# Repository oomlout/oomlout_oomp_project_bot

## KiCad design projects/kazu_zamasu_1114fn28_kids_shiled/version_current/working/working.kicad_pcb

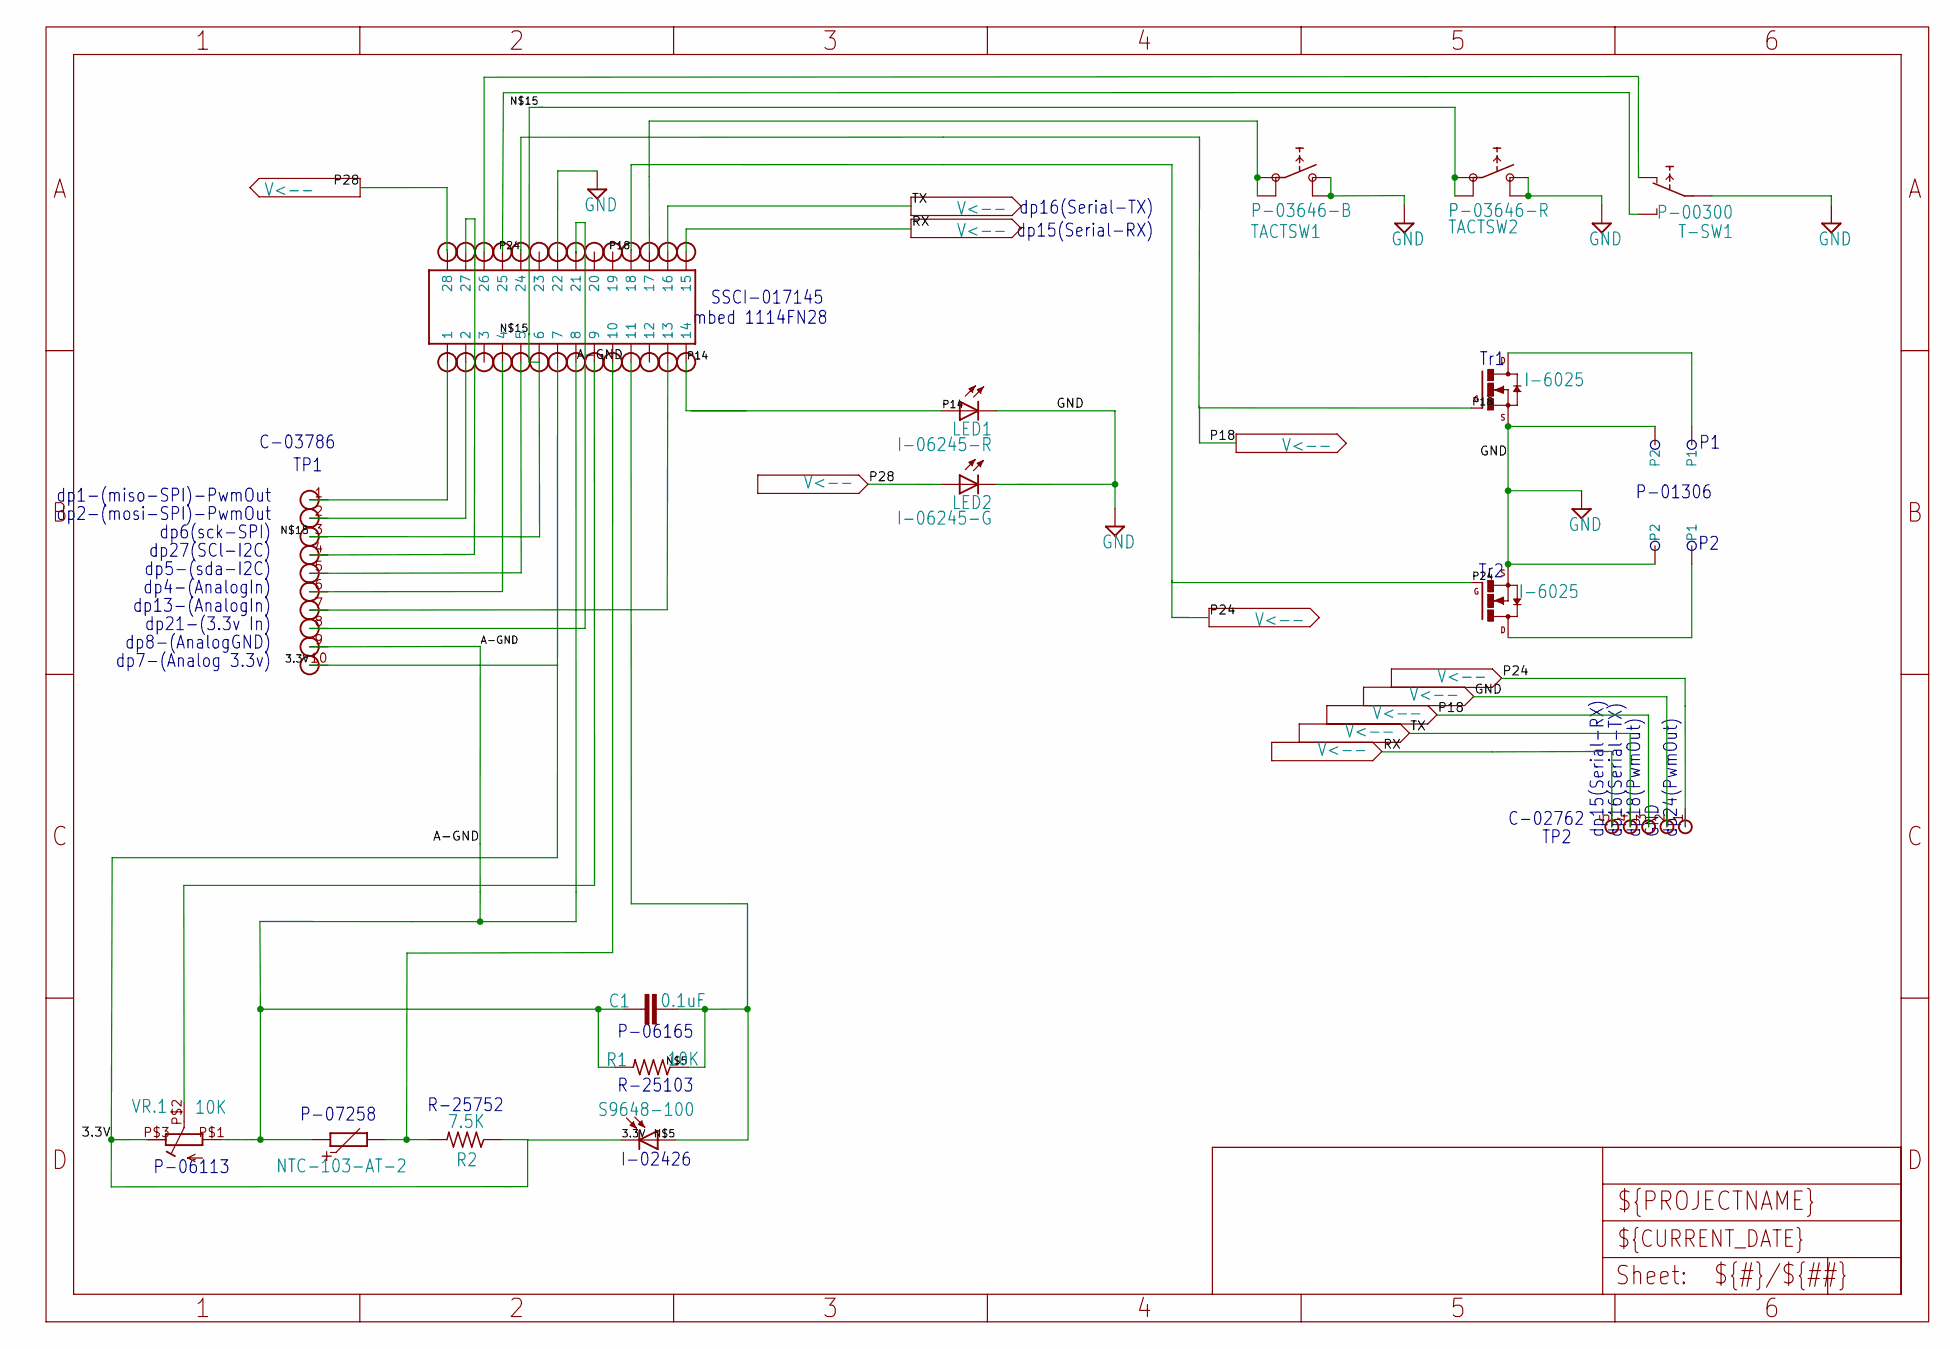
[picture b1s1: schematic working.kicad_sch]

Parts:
C1: 0.1uF; C
LED1: I-06245-R; LED5MM
LED2: I-06245-G; LED5MM
R1: 10K; R12MM
R2: 7.5K; R12MM
T-SW1: P-00300; TOGLE-SW
TACTSW1: P-03646-B; TACT-SW
TACTSW2: P-03646-R; TACT-SW
TB1, TB2: P-01306; TB
U$1: FH-1X14; DIP28-SOCKET
U$2: S9648-100; PHOTO-IC
U$3: SIPS-5
U$4, U$5: I-6025; TO251AA
U$8: SIPS-10
UNK0-50C0: NTC-103-AT-2; NTC
VR.1: 10K; VOL-TRIM

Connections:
3.3V: R2.1, U$1.P$7 (7), U$2.P$2 (C), U$8.10, VR.1.P$3 (E)
A-GND: C1.1, R1.2, U$1.P$8 (8), U$8.9, UNK0-50C0.1, VR.1.P$1 (A)
GND: LED1.K (C), LED2.K (C), T-SW1.P$2 (2COM), TACTSW1.1 (4), TACTSW1.2, TACTSW2.1 (4), TACTSW2.2, TB1.P$2 (P2), TB2.P$2 (P2), U$1.P$22 (22), U$3.2, U$4.3 (S), U$5.3 (S)
unnamed: C1.2, R1.1, U$1.P$11 (11), U$2.P$1 (A)
unnamed: U$1.P$9 (9), VR.1.P$2 (S)
unnamed: TACTSW1.3, TACTSW1.4 (1), U$1.P$17 (17)
unnamed: U$1.P$1 (1), U$8.1
unnamed: U$1.P$5 (5), U$8.5
unnamed: U$1.P$27 (27), U$8.4
unnamed: T-SW1.P$3 (3), U$1.P$25 (25)
unnamed: U$1.P$2 (2), U$8.2
unnamed: TACTSW2.3, TACTSW2.4 (1), U$1.P$6 (6), U$8.3
unnamed: U$1.P$4 (4), U$8.6
unnamed: T-SW1.P$1 (1), U$1.P$26 (26)
unnamed: TB2.P$1 (P1), U$5.2 (D), U$5.4 (D)
unnamed: TB1.P$1 (P1), U$4.2 (D), U$4.4 (D)
unnamed: U$1.P$13 (13), U$8.7
unnamed: R2.2, U$1.P$10 (10), UNK0-50C0.2
unnamed: U$1.P$21 (21), U$8.8
P14: LED1.A, U$1.P$14 (14)
P28: LED2.A, U$1.P$28 (28)
RX: U$1.P$15 (15), U$3.5
TX: U$1.P$16 (16), U$3.4

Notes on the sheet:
TP1
dp18(PwmOut)
P-06165
P-07258
R-25752
TP2
I-02426
SSCI-017145
dp21-(3.3v In)
R-25103
P-01306
dp4-(AnalogIn)
dp24(PwmOut)
GND
dp27(SCl-I2C)
Tr2
dp2-(mosi-SPI)-PwmOut
dp16(Serial-TX)
dp8-(AnalogGND)
P-06113
dp7-(Analog 3.3v)
dp13-(AnalogIn)
C-02762
dp15(Serial-RX)
mbed 1114FN28
C-03786
dp6(sck-SPI)
dp5-(sda-I2C)
dp1-(miso-SPI)-PwmOut
Tr1

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
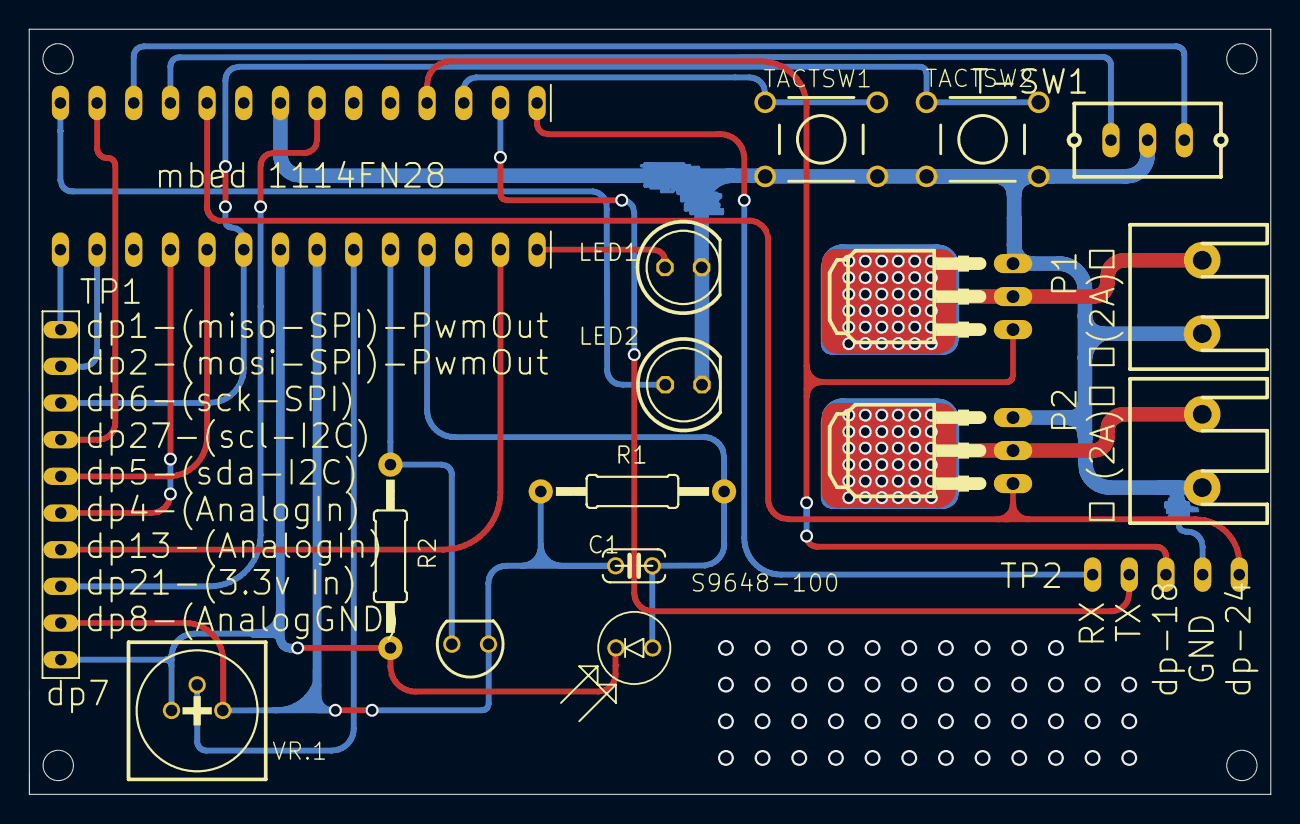
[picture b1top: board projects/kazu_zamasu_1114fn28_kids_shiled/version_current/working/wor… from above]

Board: 2 copper layers, 86.0 x 53.0 mm, 23 parts (1 on the bottom side), 25 nets.

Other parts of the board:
@HOLE0, @HOLE1, @HOLE2, @HOLE3: (no value)
U$7: A4L-LOC

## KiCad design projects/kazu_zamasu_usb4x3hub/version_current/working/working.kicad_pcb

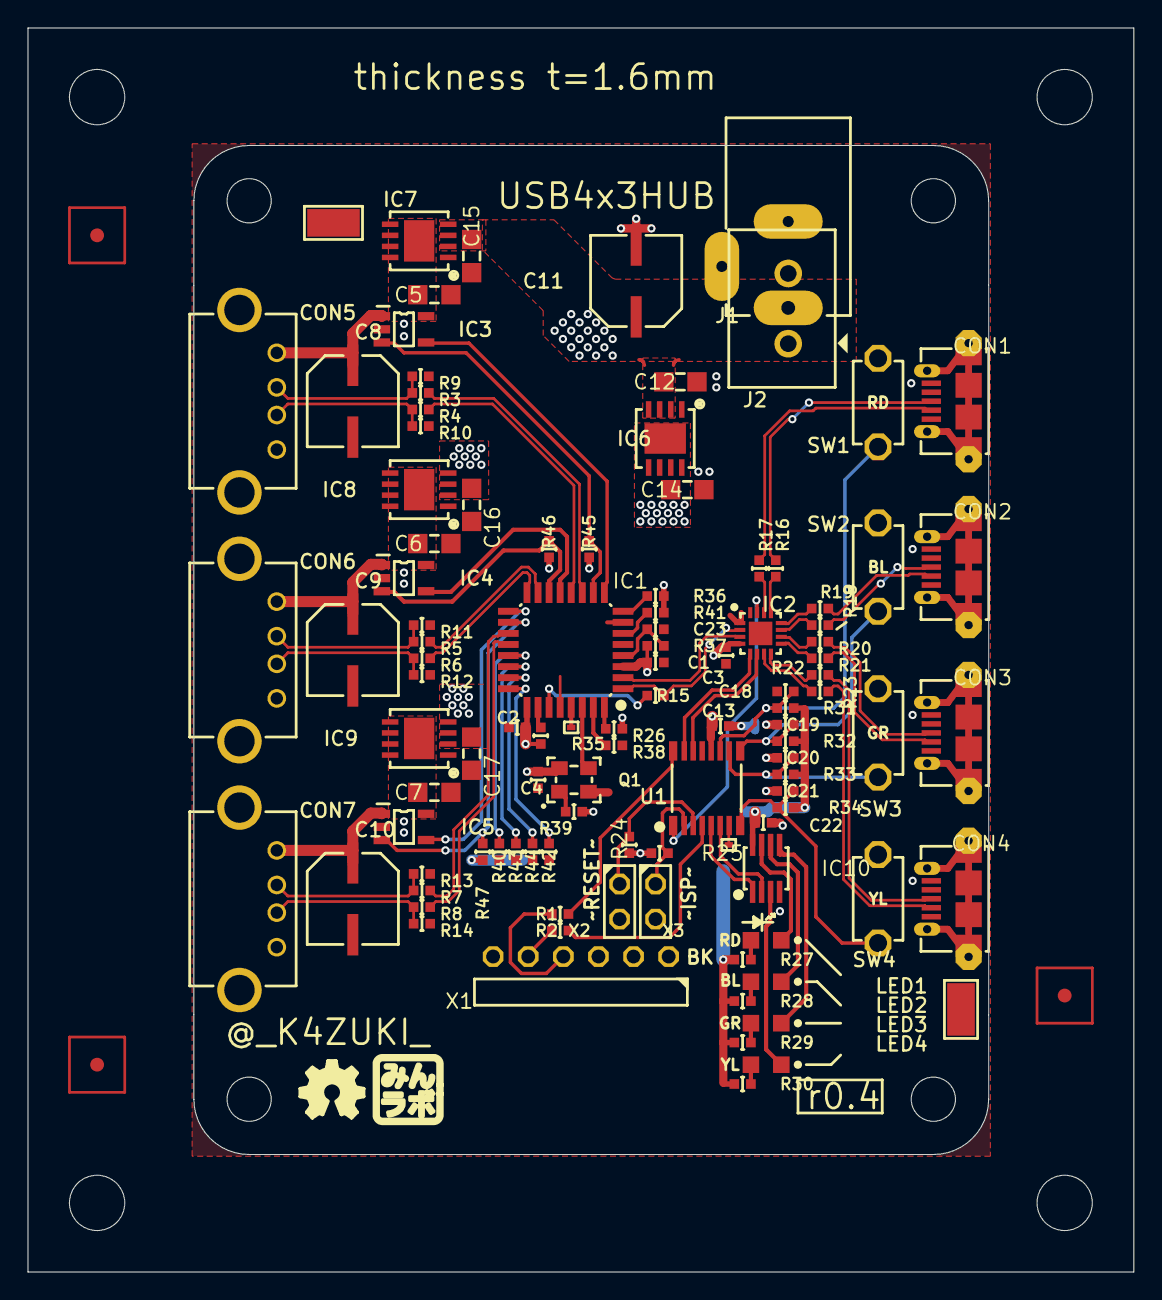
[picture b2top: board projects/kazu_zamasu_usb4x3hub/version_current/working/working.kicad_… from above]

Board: 2 copper layers, 80.0 x 90.0 mm, 121 parts (0 on the bottom side), 87 nets.

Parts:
@HOLE0, @HOLE1, @HOLE2, @HOLE3: (no value)
C1, C2, C3, C4, C13, C22: C0402
C5, C6, C7, C12, C14, C15, C16, C17: 4.7u/2012; CR_2125
C8, C9, C10, C11: 100u/OS-CON; C_2.5PHI6.3_C6
C18, C19, C20, C21: 0.1u/1005; C0402
C23: 1u/1005; C0402
CON1, CON2, CON3, CON4: CON_USB_47589-0001MOLEX
CON5, CON6, CON7: CON_USB_A_SHIELD
GIT1: 27149e3; GIT-REVISION
I1: ICON_MINLAB_5.2MM
IC1: TUSB2036; QFP32_0.8P7.2X7.2
IC2: FSUSB74MPX; QFN16_0.5P3.0X3.0
IC3, IC4, IC5: TPS2041C; IC_05_0.95_50MIL
IC6: 3.3V; DFN80P410X410_8N
IC7, IC8, IC9: 5V; DFN80P410X410_8N
IC10: SN74LVC1G139DCUR; SOT65P315X290-8N
ICON1: OSHW; ICON_OSHW
ICON2: r0.4; ICON_REVISION2.0
J1: CON_DCJACK_C-1604
J2: TB111-2-2-U-1-1
LED1: RD; CHIPLED_0805
LED2: BL; CHIPLED_0805
LED3: GR; CHIPLED_0805
LED4: YL; CHIPLED_0805
P1, P2, P3, P4: PCB_CORNER
Q1: OSC4_48M; CLOCK_2520
R1, R2, R9, R10, R11, R12, R13, R14, R24, R25, R26, R27, R28, R29, R30, R31, R32, R33, R34, R35, R36, R37, R38, R40, R41, R42, R43, R44, R45, R46, R47: C0402
R3, R4, R5, R6, R7, R8, R16, R17, R18, R19, R20, R21, R22, R23: 33/1005; C0402
R15: 1.5k/1005; C0402
R39: 10k/1005; C0402
SW1: RD; SW_TACTSW_P8073
SW2: BL; SW_TACTSW_P8073
SW3: GR; SW_TACTSW_P8073
SW4: YL; SW_TACTSW_P8073
TP1, TP2: TP_4020
TP3, TP4: TP06RECT
TP100, TP101, TP102: FIDUCIAL
U1: LPC812M101JDH16; SOT65P510X450X110-16N
X1: TSW-106-02-S-S-RA
X2, X3: TSW-102-02-S-S

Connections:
3.3V: C1.1, C2.1, C3.1, C4.1, C13.2, C14.1, C22.1, IC1.3, IC1.25, IC2.4, IC6.5, IC6.6, IC6.7, IC6.EP, IC10.8, Q1.4, R24.2, R25.2, R26.1, R27.2, R28.2, R29.2, R30.2, R31.2, R32.2, R33.2, R34.2, R35.1, R36.1, R37.1, R39.1, R41.2, R45.2, R46.2, R47.2, U1.12
5V1: C5.1, IC3.5, IC7.5, IC7.6, IC7.7, IC7.EP
5V2: C6.1, IC4.5, IC8.5, IC8.6, IC8.7, IC8.EP
5V3: C7.1, IC5.5, IC9.5, IC9.6, IC9.7, IC9.EP
->TX: R1.1, X1.4
<-RX: R2.1, X1.5
GND: C1.2, C2.2, C3.2, C4.2, C5.2, C6.2, C7.2, C8.-, C9.-, C10.-, C11.-, C12.2, C13.1, C14.2, C15.2, C16.2, C17.2, C18.2, C19.2, C20.2, C21.2, C22.2, C23.2, CON1.5, CON2.5, CON3.5, CON4.5, CON5.4, CON6.4, CON7.4, IC1.7, IC1.28, IC2.1, IC3.2, IC4.2, IC5.2, IC6.1, IC7.1, IC8.1, IC9.1, IC10.4, J1.1, J2.2, Q1.2, R9.1, R10.1, R11.1, R12.1, R13.1, R14.1, R38.1, R40.1, R42.1, R43.1, R44.1, SW1.A1, SW2.A1, SW3.A1, SW4.A1, TP1.TP, TP2.TP, U1.13, X1.1, X2.2, X3.2
ISP: R25.1, U1.2, X3.1
LSEL1: IC10.1, U1.5
LSEL2: IC10.2, U1.6
unnamed: IC1.1, IC2.2, R15.1
unnamed: IC1.2, IC2.3
unnamed: CON1.3, R16.1
unnamed: CON1.2, R17.1
unnamed: CON2.3, R18.1
unnamed: CON2.2, R19.1
unnamed: CON3.3, R20.1
unnamed: CON4.3, R22.1
unnamed: CON3.2, R21.1
unnamed: CON4.2, R23.1
unnamed: C8.+, CON5.1, IC3.1
unnamed: C9.+, CON6.1, IC4.1
unnamed: C10.+, CON7.1, IC5.1
unnamed: IC1.30, Q1.3
unnamed: IC1.10, IC3.3, R45.1
unnamed: IC1.9, IC3.4
unnamed: CON5.2, R3.2, R9.2
unnamed: CON5.3, R4.2, R10.2
unnamed: IC1.14, IC4.3, R46.1
unnamed: IC1.13, IC4.4
unnamed: CON6.2, R5.2, R11.2
unnamed: CON6.3, R6.2, R12.2
unnamed: IC1.17, IC5.4
unnamed: IC1.18, IC5.3, R47.1
unnamed: CON7.2, R7.2, R13.2
unnamed: CON7.3, R8.2, R14.2
unnamed: IC1.6, R41.1
unnamed: CON1.SHD, CON1.SHD$1, CON1.SHD$2, CON1.SHD$3, CON1.SHD$4, CON1.SHD$5, CON1.SHD$6, CON1.SHD$7
unnamed: CON2.SHD, CON2.SHD$1, CON2.SHD$2, CON2.SHD$3, CON2.SHD$4, CON2.SHD$5, CON2.SHD$6, CON2.SHD$7
unnamed: CON3.SHD, CON3.SHD$1, CON3.SHD$2, CON3.SHD$3, CON3.SHD$4, CON3.SHD$5, CON3.SHD$6, CON3.SHD$7
unnamed: CON4.SHD, CON4.SHD$1, CON4.SHD$2, CON4.SHD$3, CON4.SHD$4, CON4.SHD$5, CON4.SHD$6, CON4.SHD$7
unnamed: IC1.11, R3.1
unnamed: IC1.12, R4.1
unnamed: IC1.15, R5.1
unnamed: IC1.16, R6.1
unnamed: IC1.19, R7.1
unnamed: IC1.20, R8.1
unnamed: IC1.27, R15.2
unnamed: IC2.13, R16.2
unnamed: IC2.11, R18.2
unnamed: IC2.10, R20.2
unnamed: IC2.8, R22.2
unnamed: IC2.14, R17.2
unnamed: IC2.12, R19.2
unnamed: IC2.9, R21.2
unnamed: IC2.7, R23.2
unnamed: IC1.32, R26.2
unnamed: IC10.7, LED1.C
unnamed: IC10.6, LED2.C
unnamed: IC10.5, LED3.C
unnamed: IC10.3, LED4.C
unnamed: LED4.A, R30.1
unnamed: LED3.A, R29.1
unnamed: LED2.A, R28.1
unnamed: LED1.A, R27.1
unnamed: IC1.29, TP3.TP
unnamed: IC1.26, R35.2
unnamed: IC1.8, R36.2
unnamed: C23.1, IC1.4, R37.2
unnamed: IC1.31, R38.2
unnamed: IC1.21, R40.2
unnamed: IC1.24, R42.2
unnamed: IC1.23, R44.2
unnamed: IC1.22, R43.2
unnamed: Q1.1, R39.2
unnamed: TP4.TP, U1.7
SEL0: IC2.6, U1.14
SEL1: IC2.5, U1.15
SW1: C18.1, R31.1, SW1.A2, U1.11
SW2: C19.1, R32.1, SW2.A2, U1.9
SW3: C20.1, R33.1, SW3.A2, U1.10
SW4: C21.1, R34.1, SW4.A2, U1.8
TGT_RX: R1.2, U1.16
TGT_TX: R2.2, U1.4
VIN: C11.+, C12.1, C15.1, C16.1, C17.1, IC6.2, IC6.3, IC6.4, IC7.2, IC7.3, IC7.4, IC8.2, IC8.3, IC8.4, IC9.2, IC9.3, IC9.4, J1.3, J2.1
~OE: IC2.15, U1.1
~RESET: R24.1, U1.3, X2.1

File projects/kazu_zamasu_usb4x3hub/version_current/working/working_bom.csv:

"Id";"Designator";"Footprint";"Quantity";"Designation";"Supplier and ref";
1;"C22,R30,R29,R40,R24,C3,R45,R11,R33,R1,R37,C13,R10,C4,R35,R25,R14,R9,R38,R44,R42,R13,R28,R46,R34,R27,R43,R47,R26,R12,R36,R2,R31,R41,C2,C1,R32";"C0402";37;"";;;
2;"C8,C11,C9,C10";"C_2.5PHI6.3_C6";4;"100u/OS-CON";;;
3;"X3,X2";"TSW-102-02-S-S";2;"TSW-102-02-S-S";;;
4;"TP3,TP4";"TP06RECT";2;"";;;
5;"@HOLE0,@HOLE1,@HOLE2,@HOLE3";"";4;"";;;
6;"IC6";"DFN80P410X410_8N";1;"3.3V";;;
7;"J2";"TB111-2-2-U-1-1";1;"";;;
8;"C17,C12,C14,C6,C16,C7,C5,C15";"CR_2125";8;"4.7u/2012";;;
9;"R16,R22,R21,R17,R8,R7,R3,R4,R19,R6,R18,R20,R5,R23";"C0402";14;"33/1005";;;
10;"LED2";"CHIPLED_0805";1;"BL";;;
11;"ICON2";"ICON_REVISION2.0";1;"r0.4";;;
12;"P2,P4,P1,P3";"PCB_CORNER";4;"";;;
13;"LED3";"CHIPLED_0805";1;"GR";;;
14;"TP101,TP102,TP100";"FIDUCIAL";3;"";;;
15;"GIT1";"GIT-REVISION";1;"27149e3";;;
16;"I1";"ICON_MINLAB_5.2MM";1;"";;;
17;"SW4";"SW_TACTSW_P8073";1;"YL";;;
18;"IC10";"SOT65P315X290-8N";1;" SN74LVC1G139DCUR";;;
19;"CON2,CON1,CON3,CON4";"CON_USB_47589-0001MOLEX";4;"";;;
20;"ICON1";"ICON_OSHW";1;"OSHW";;;
21;"IC9,IC7,IC8";"DFN80P410X410_8N";3;"5V";;;
22;"C21,C18,C20,C19";"C0402";4;"0.1u/1005";;;
23;"IC4,IC5,IC3";"IC_05_0.95_50MIL";3;"TPS2041C";;;
24;"TP2,TP1";"TP_4020";2;"";;;
25;"C23";"C0402";1;"1u/1005";;;
26;"CON5,CON7,CON6";"CON_USB_A_SHIELD";3;"";;;
27;"SW3";"SW_TACTSW_P8073";1;"GR";;;
28;"LED4";"CHIPLED_0805";1;"YL";;;
29;"J1";"CON_DCJACK_C-1604";1;"";;;
30;"X1";"TSW-106-02-S-S-RA";1;"TSW-106-02-S-S-RA";;;
31;"SW1";"SW_TACTSW_P8073";1;"RD";;;
32;"U1";"SOT65P510X450X110-16N";1;"LPC812M101JDH16";;;
33;"SW2";"SW_TACTSW_P8073";1;"BL";;;
34;"IC2";"QFN16_0.5P3.0X3.0";1;"FSUSB74MPX";;;
35;"IC1";"QFP32_0.8P7.2X7.2";1;"TUSB2036";;;
36;"LED1";"CHIPLED_0805";1;"RD";;;
37;"R15";"C0402";1;"1.5k/1005";;;
38;"Q1";"CLOCK_2520";1;"OSC4_48M";;;
39;"R39";"C0402";1;"10k/1005";;;

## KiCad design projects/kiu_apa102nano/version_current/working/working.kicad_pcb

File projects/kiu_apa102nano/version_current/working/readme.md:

# OOMP Project  
## apa102nano  by kiu  
  
oomp key: oomp_projects_flat_kiu_apa102nano  
(snippet of original readme)  
  
- apa102nano  
I love to play around with adressable [APA102](https://cpldcpu.wordpress.com/2014/08/27/apa102/) LED strips, quickly iterating animations using the Arduino Nano.  
But I am tired of wiring power, looking up which pins are SPI and having dangling wires everywhere. Time to have some boards ready for a frustration free out-of-the-box experience.  

- Nitty-Gritty Details  
Checkout the [pics](https://github.com/kiu/apa102nano/tree/master/pics) and [hardware](https://github.com/kiu/apa102nano/tree/master/rev_a) section including BOM, Schematic, PCB layout, etc.  
  
- Errata  
I included mounting holes as an afterthought and forget to hide the silk screen "REF**" designators :/  
  
- License  
Creative Commons Attribution-NonCommercial 3.0 Unported (CC BY-NC 3.0)  
See LICENSE and https://creativecommons.org/licenses/by-nc/3.0/  
  
  full source readme at [readme_src.md](readme_src.md)  
  
source repo at: [https://github.com/kiu/apa102nano](https://github.com/kiu/apa102nano)  
## Board  

## Schematic  

[schematic pdf](working_schematic.pdf)  
## Images

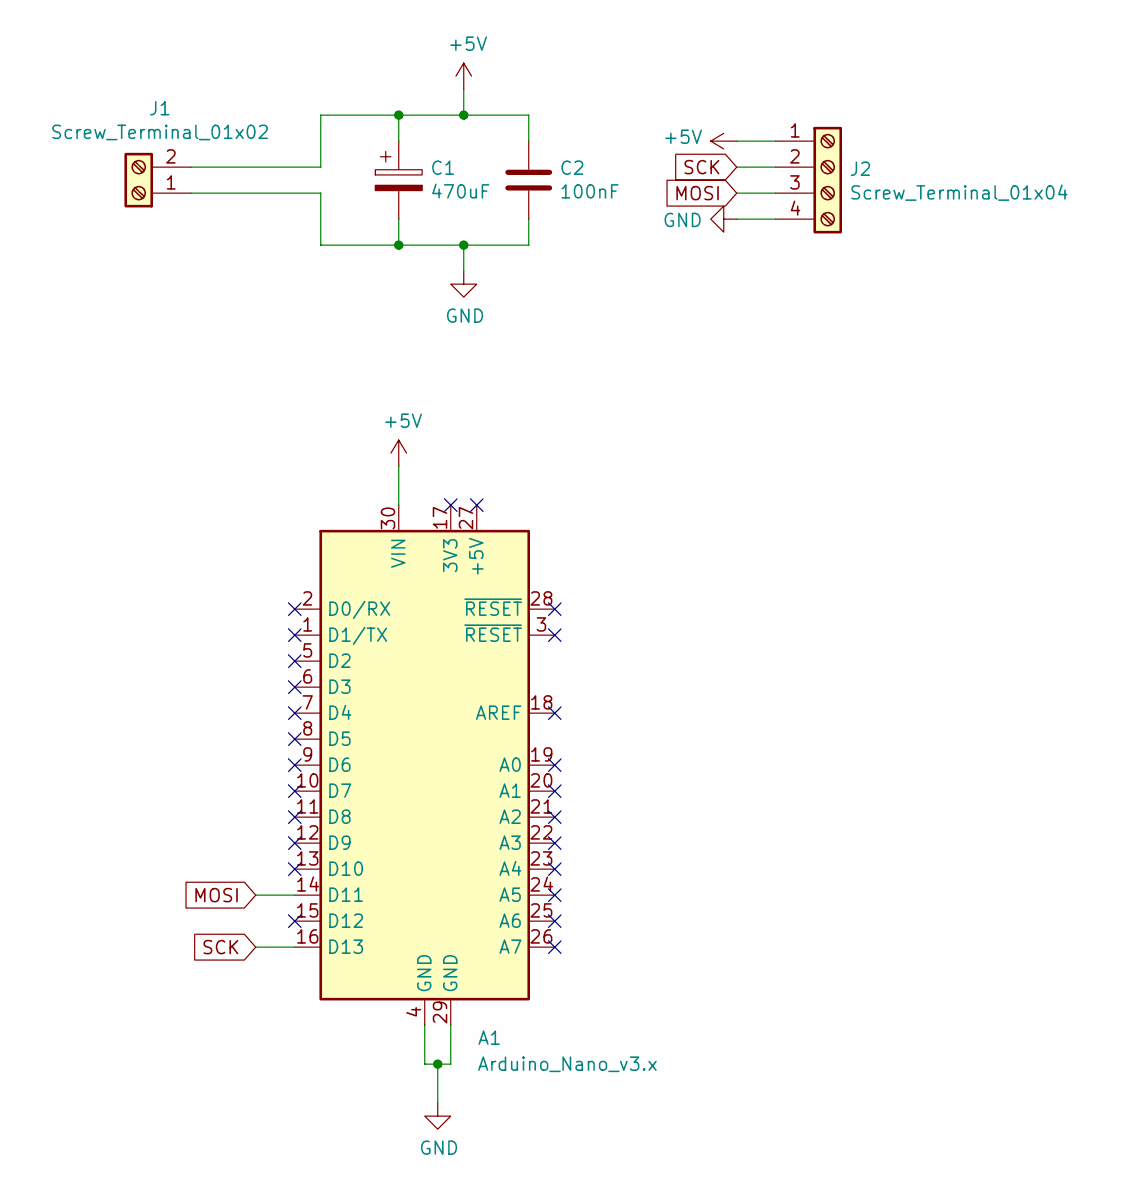
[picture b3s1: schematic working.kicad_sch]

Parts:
A1: Arduino_Nano_v3.x; Arduino_Nano
C1: 470uF; CP_Tantalum_Case-D_EIA-7343-31_Hand
C2: 100nF; C_0805_HandSoldering
J1: Screw_Terminal_01x02; TerminalBlock_bornier-2_P5.08mm
J2: Screw_Terminal_01x04; TerminalBlock_bornier-4_P5.08mm

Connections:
+5V: A1.30 (VIN), C1.1, C2.1, J1.2, J2.1
GND: A1.4 (GND), A1.29 (GND), C1.2, C2.2, J1.1, J2.4
MOSI: A1.14 (D11), J2.3
SCK: A1.16 (D13), J2.2

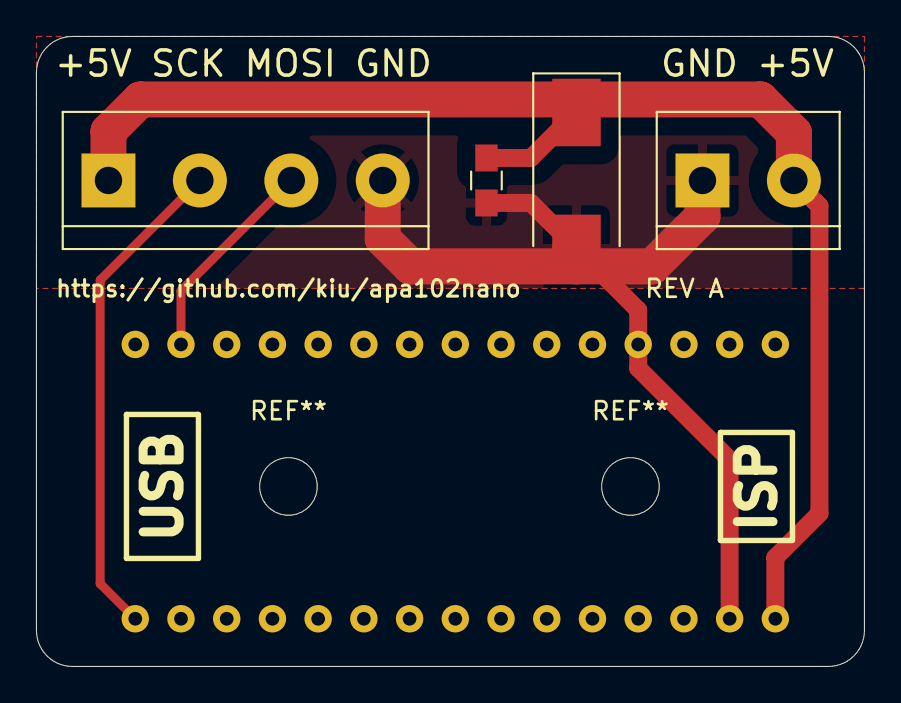
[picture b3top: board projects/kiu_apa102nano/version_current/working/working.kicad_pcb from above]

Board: 2 copper layers, 46.0 x 35.0 mm, 5 parts (0 on the bottom side), 4 nets.

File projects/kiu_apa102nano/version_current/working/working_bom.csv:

"Id";"Designator";"Footprint";"Quantity";"Designation";"Supplier and ref";
1;"C2";"C_0805_HandSoldering";1;"100nF";;;
2;"A1";"Arduino_Nano";1;"Arduino_Nano_v3.x";;;
3;"J1";"TerminalBlock_bornier-2_P5.08mm";1;"Screw_Terminal_01x02";;;
4;"C1";"CP_Tantalum_Case-D_EIA-7343-31_Hand";1;"470uF";;;
5;"J2";"TerminalBlock_bornier-4_P5.08mm";1;"Screw_Terminal_01x04";;;

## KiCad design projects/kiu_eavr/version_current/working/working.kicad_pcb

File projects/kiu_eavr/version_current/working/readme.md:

# OOMP Project  
## eAVR  by kiu  
  
oomp key: oomp_projects_flat_kiu_eavr  
(snippet of original readme)  

- eAVR  
  
eAVR (**e**dge AVR) replaces the standard 6P (2x03) pinheader or 6P (2x03) IDC socket for AVR device programming and debugging (aWire, PDI, SPI, TPI, UPDI) with an edge connector, reducing your BOM costs and soldering efforts.  
  
Besides the card edge footprints this project includes adapter boards to interface the standard AVR 6P connector to the required card egde connectors.  
  
-- Content  
  
This repository features footprints, adapters and example boards.  
  
* [eAVR.pretty](https://github.com/kiu/eAVR/tree/main/eAVR.pretty): Footprints for KiCad   
* [eAVR6-adapter-hrz](https://github.com/kiu/eAVR/tree/main/eAVR6-adapter-hrz): A card edge to 6pin horizontal adapter   
* [eAVR6-adapter-vrt](https://github.com/kiu/eAVR/tree/main/eAVR6-adapter-vrt): A card edge to 6pin vertical adapter  
* [eAVR6-example](https://github.com/kiu/eAVR/tree/main/eAVR6-example): An example board using TPI   
* [eAVR6-UPDI-adapter](https://github.com/kiu/eAVR/tree/main/eAVR6-UPDI-adapter): A card edge to 6pin adapter for UDPI only  
* [eAVR6-UPDI-example](https://github.com/kiu/eAVR/tree/main/eAVR6-UPDI-example): An example board using UPDI  
  
-- Disclaimer  
  
This is NOT an official standard or related to anything official by Microchip Technology Incorporated. This is a hobby standardization attempt to improve the quality of life for AVR developers.  
  
--  Wear and tear  
  
Be aware that with "cheap" PCB fabrication, your edge con  
  full source readme at [readme_src.md](readme_src.md)  
  
source repo at: [https://github.com/kiu/eAVR](https://github.com/kiu/eAVR)  
## Board  

## Schematic  

[schematic pdf](working_schematic.pdf)  
## Images

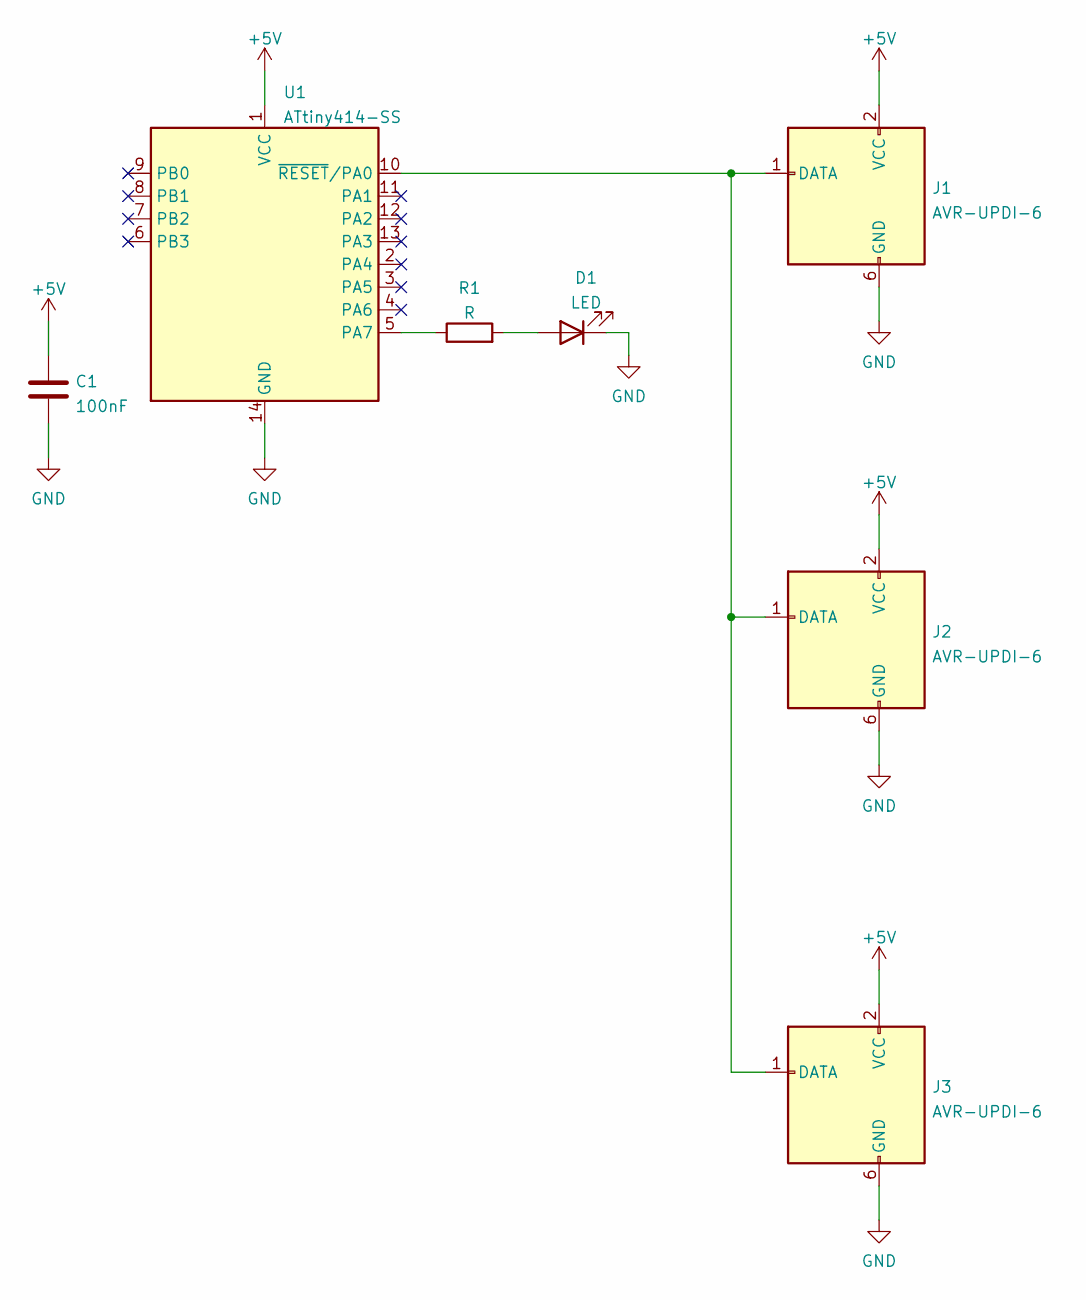
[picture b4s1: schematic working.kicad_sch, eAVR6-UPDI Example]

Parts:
C1: 100nF; C_0805_2012Metric
D1: LED; LED_0805_2012Metric
J1: AVR-UPDI-6; eAVR6-UPDI-F
J2: AVR-UPDI-6; eAVR6-UPDI-FB
J3: AVR-UPDI-6; eAVR6-UPDI-B
R1: R; R_0805_2012Metric
U1: ATtiny414-SS; SOIC-14_3.9x8.7mm_P1.27mm

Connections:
+5V: C1.1, J1.2 (VCC), J2.2 (VCC), J3.2 (VCC), U1.1 (VCC)
GND: C1.2, D1.1 (K), J1.6 (GND), J2.6 (GND), J3.6 (GND), U1.14 (GND)
unnamed: D1.2 (A), R1.2
unnamed: J1.1 (DATA), J2.1 (DATA), J3.1 (DATA), U1.10 (~RESET/PA0)
unnamed: R1.1, U1.5 (PA7)

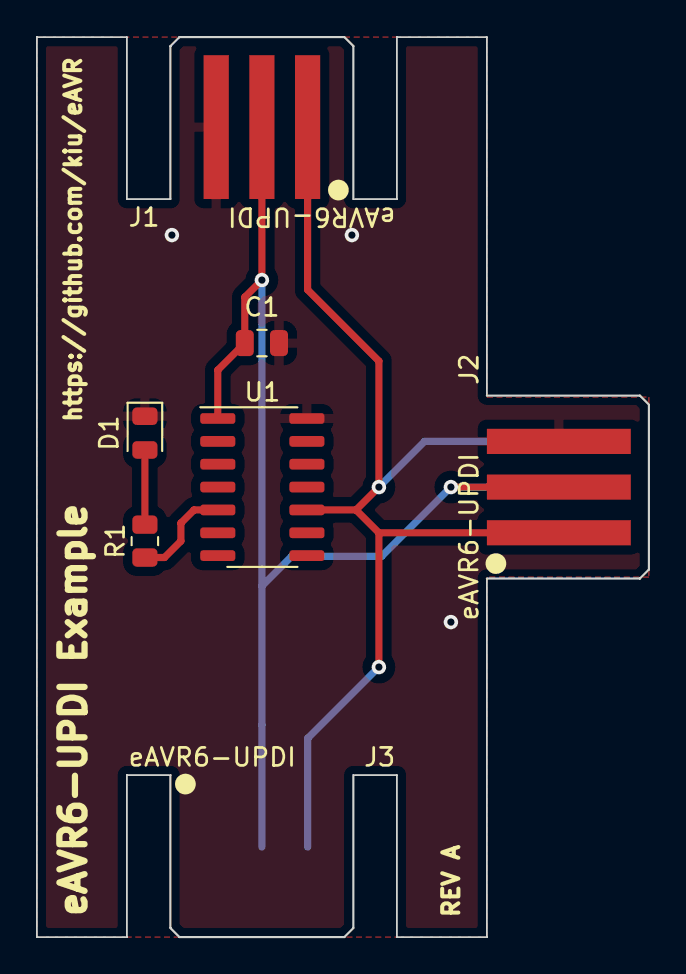
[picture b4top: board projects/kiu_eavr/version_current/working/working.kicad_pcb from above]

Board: 2 copper layers, 34.0 x 50.0 mm, 7 parts (0 on the bottom side), 5 nets.

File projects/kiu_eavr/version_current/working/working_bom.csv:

"Id";"Designator";"Footprint";"Quantity";"Designation";"Supplier and ref";
1;"C1";"C_0805_2012Metric";1;"100nF";;;
2;"J3";"eAVR6-UPDI-B";1;"AVR-UPDI-6";;;
3;"J1";"eAVR6-UPDI-F";1;"AVR-UPDI-6";;;
4;"R1";"R_0805_2012Metric";1;"R";;;
5;"U1";"SOIC-14_3.9x8.7mm_P1.27mm";1;"ATtiny414-SS";;;
6;"J2";"eAVR6-UPDI-FB";1;"AVR-UPDI-6";;;
7;"D1";"LED_0805_2012Metric";1;"LED";;;

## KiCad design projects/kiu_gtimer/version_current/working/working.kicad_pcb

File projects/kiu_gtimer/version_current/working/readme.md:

# gtimer by kiu  
This is a harvested standardized copy of a project from github.  
The original project can be found at:  
https://github.com/kiu/gtimer  
Please consult that link for additional, details, files, and license information.  
Note: It was auto harvested and if the original repo had more than one board file or anything out of the ordinary the files here are likely not representative.

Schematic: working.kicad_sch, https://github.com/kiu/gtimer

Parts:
C1, C2, C4: 100nF; C_0805_HandSoldering
C3, C5: 10uF; CP_Tantalum_Case-D_EIA-7343-31_Hand
D1: BAV99; SOT-23-3
H1, H2, H3: MountingHole; MountingHole_4.3mm_M4
H5, H6: MountingHole; MountingHole_3.2mm_M3
JDBG1: Conn_01x03; Pin_Header_Straight_1x03_Pitch2.54mm
JHTU1: Conn_01x04; Pin_Header_Straight_1x04_Pitch2.54mm
JISP1: Conn_02x03_Odd_Even; Pin_Header_Straight_2x03_Pitch2.54mm
JNOW1: Conn_01x04; Pin_Header_Straight_1x05_Pitch2.54mm
JPMP1: Screw_Terminal_01x02; TerminalBlock_bornier-2_P5.08mm
JPWR1: Conn_01x02; Pin_Header_Straight_1x02_Pitch2.54mm
JPWR2: Screw_Terminal_01x02; TerminalBlock_bornier-2_P5.08mm
JRTC1: Conn_01x05; Pin_Header_Straight_1x05_Pitch2.54mm
JWAIT1: Conn_01x04; Pin_Header_Straight_1x05_Pitch2.54mm
Q1: BC847; SOT-23-3
R1, R3, R4: 10k; R_0805_HandSoldering
R2: 1k; R_0805_HandSoldering
RL1: G2RL-24-DC5; Relay_DPDT_Omron_G2RL-24
U1: ATmega328PB-AU; LQFP-32_7x7mm_Pitch0.8mm
U2: NCP1117ST50T3G; SOT-223; MPN NCP1117ST50T3G; Digi-Key_PN NCP1117ST50T3GOSCT-ND

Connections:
+5V: C2.1, C5.1, JHTU1.1, JISP1.2, JPWR1.1, JRTC1.1, Q1.3 (C), R1.1, R3.1, R4.1, U1.4, U1.18, U2.2, U2.4
+15V: C3.1, JPWR2.1, RL1.3, U2.3
BTN_NOW: JNOW1.1, U1.23
BTN_NOW_LED: JNOW1.2, U1.24
BTN_WAIT: JWAIT1.1, U1.25
BTN_WAIT_LED: JWAIT1.2, U1.26
DBG_RX: JDBG1.1, U1.30
DBG_TX: JDBG1.2, U1.31
GND: C1.1, C2.2, C3.2, C4.2, C5.2, D1.1 (K), JDBG1.3, JHTU1.2, JISP1.6, JNOW1.3, JNOW1.4, JPWR1.2, JPWR2.2, JRTC1.5, JWAIT1.3, JWAIT1.4, RL1.6, RL1.8, U1.5, U1.21, U2.1
ISP_MISO: JISP1.1, U1.16
ISP_MOSI: JISP1.4, U1.15
ISP_RES: C4.1, JISP1.5, R1.2, U1.29
ISP_SCK: JISP1.3, U1.17
unnamed: C1.2, U1.20
unnamed: D1.2 (A), Q1.2 (E), RL1.1
unnamed: JPMP1.1, RL1.4
unnamed: JPMP1.2, RL1.5
unnamed: Q1.1 (B), R2.1
RELAY: R2.2, U1.12
TWI_SCL: JHTU1.3, JRTC1.3, R3.2, U1.28
TWI_SDA: JHTU1.4, JRTC1.2, R4.2, U1.27

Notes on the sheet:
Optional
RTC
Power
HTU21

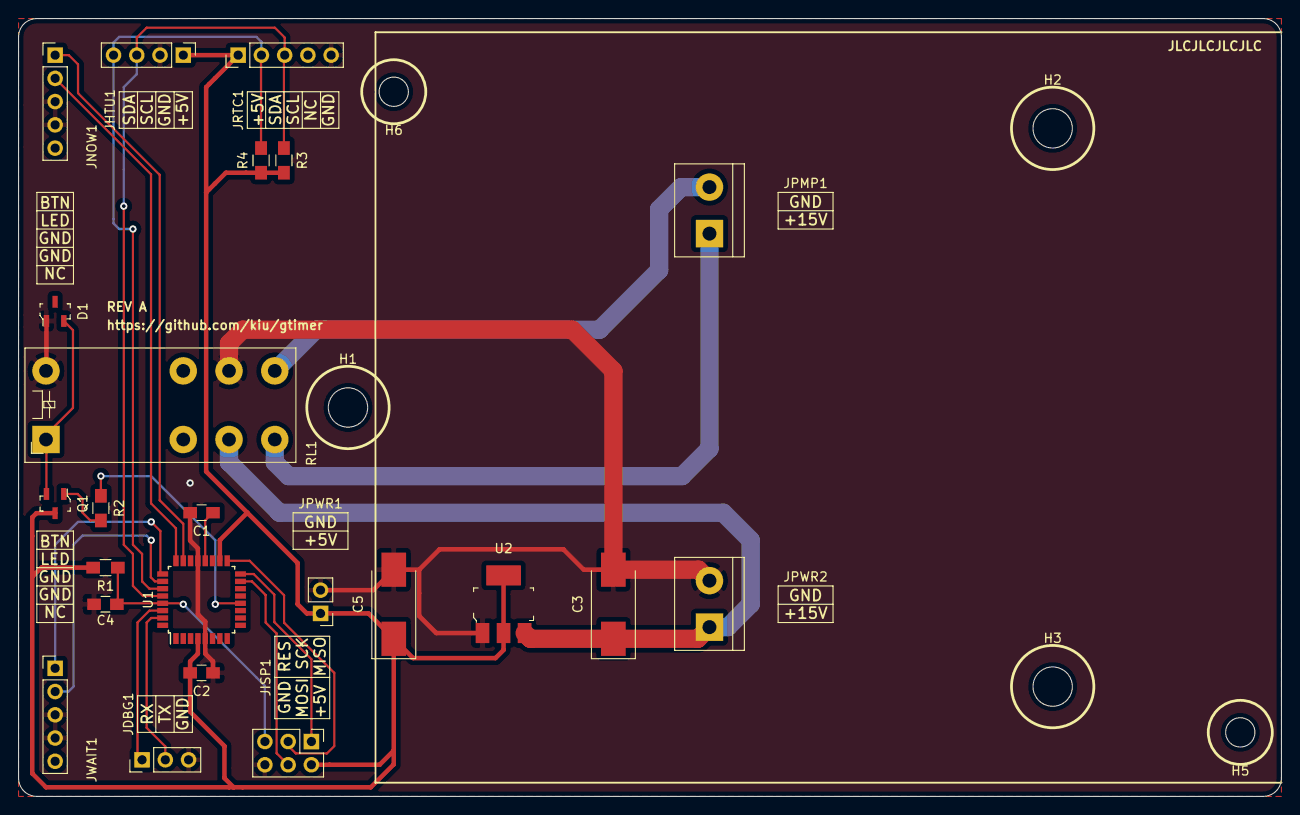
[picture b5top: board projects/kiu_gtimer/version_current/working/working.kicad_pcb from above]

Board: 2 copper layers, 138.0 x 85.0 mm, 28 parts (0 on the bottom side), 21 nets.

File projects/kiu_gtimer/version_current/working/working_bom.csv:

"Id";"Designator";"Footprint";"Quantity";"Designation";"Supplier and ref";
1;"JWAIT1,JNOW1";"Pin_Header_Straight_1x05_Pitch2.54mm";2;"Conn_01x04";;;
2;"D1";"SOT-23-3";1;"BAV99";;;
3;"JRTC1";"Pin_Header_Straight_1x05_Pitch2.54mm";1;"Conn_01x05";;;
4;"JPMP1,JPWR2";"TerminalBlock_bornier-2_P5.08mm";2;"Screw_Terminal_01x02";;;
5;"U2";"SOT-223";1;"NCP1117ST50T3G";;;
6;"U1";"LQFP-32_7x7mm_Pitch0.8mm";1;"ATmega328PB-AU";;;
7;"RL1";"Relay_DPDT_Omron_G2RL-24";1;"G2RL-24-DC5";;;
8;"R4,R3,R1";"R_0805_HandSoldering";3;"10k";;;
9;"R2";"R_0805_HandSoldering";1;"1k";;;
10;"Q1";"SOT-23-3";1;"BC847";;;
11;"JPWR1";"Pin_Header_Straight_1x02_Pitch2.54mm";1;"Conn_01x02";;;
12;"JISP1";"Pin_Header_Straight_2x03_Pitch2.54mm";1;"Conn_02x03_Odd_Even";;;
13;"JDBG1";"Pin_Header_Straight_1x03_Pitch2.54mm";1;"Conn_01x03";;;
14;"JHTU1";"Pin_Header_Straight_1x04_Pitch2.54mm";1;"Conn_01x04";;;
15;"C5,C3";"CP_Tantalum_Case-D_EIA-7343-31_Hand";2;"10uF";;;
16;"C4,C2,C1";"C_0805_HandSoldering";3;"100nF";;;

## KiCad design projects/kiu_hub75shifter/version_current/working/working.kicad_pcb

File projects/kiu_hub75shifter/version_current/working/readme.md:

# hub75shifter by kiu  
This is a harvested standardized copy of a project from github.  
The original project can be found at:  
https://github.com/kiu/hub75shifter  
Please consult that link for additional, details, files, and license information.  
Note: It was auto harvested and if the original repo had more than one board file or anything out of the ordinary the files here are likely not representative.

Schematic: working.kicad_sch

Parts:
C1, C3, C5: 100nF; C_0805_HandSoldering
C2: 1uF; C_0805_HandSoldering
C4: 100pF; C_0805_HandSoldering
C6: 10uF; CP_Elec_4x5.7
D1: LED; LED_0805_HandSoldering
JHUB75: Conn_02x08_Odd_Even; Socket_Strip_Straight_2x08_Pitch2.54mm
JIN1: Conn_02x05_Odd_Even; Pin_Header_Straight_2x05_Pitch2.54mm
JOUT1: Conn_02x05_Odd_Even; Pin_Header_Straight_2x05_Pitch2.54mm
JPWR1: Screw_Terminal_01x02; TerminalBlock_bornier-2_P5.08mm
JSWD1: Conn_02x05_Odd_Even; Pin_Header_Straight_2x05_Pitch2.54mm
R1: 60R; R_0805_HandSoldering
R2: 1k; R_0805_HandSoldering
U1: SAMC20G17A-A; TQFP-48_7x7mm_Pitch0.5mm

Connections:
CLEAR: JIN1.5, JOUT1.5, U1.37
GND: C1.2, C2.2, C3.2, C5.2, C6.2, D1.1 (K), JHUB75.4, JHUB75.8, JHUB75.12, JHUB75.16, JIN1.8, JIN1.10, JOUT1.8, JOUT1.10, JPWR1.2, JSWD1.3, JSWD1.5, JSWD1.9, U1.5, U1.18, U1.35, U1.42
LED: R1.2, U1.48
MCU_RESET: C4.2, JSWD1.10, U1.40
unnamed: C1.1, C2.1, U1.43
unnamed: D1.2 (A), R1.1
OE: JIN1.4, JOUT1.4, U1.39
P_A: JHUB75.9, U1.25
P_B: JHUB75.10, U1.26
P_B1: JHUB75.3, U1.3
P_B2: JHUB75.7, U1.10
P_C: JHUB75.11, U1.27
P_CLK: JHUB75.13, U1.11
P_G1: JHUB75.2, U1.2
P_G2: JHUB75.6, U1.9
P_OE: JHUB75.15, U1.19
P_R1: JHUB75.1, U1.1
P_R2: JHUB75.5, U1.4
P_STB: JHUB75.14, U1.20
SHIFT: JIN1.3, JOUT1.3, U1.38
SPI0_MOSI: JOUT1.9, U1.15
SPI0_SCK: JOUT1.7, U1.16
SPI0_SS: JOUT1.6, U1.14
SPI1_MOSI: JIN1.9, U1.21
SPI1_SCK: JIN1.7, U1.22
SPI1_SS: JIN1.6, U1.23
SWDCLK: JSWD1.4, R2.2, U1.45
SWDIO: JSWD1.2, U1.46
VCC: C3.1, C4.1, C5.1, C6.1, JIN1.1, JIN1.2, JOUT1.1, JOUT1.2, JPWR1.1, JSWD1.1, R2.1, U1.6, U1.17, U1.36, U1.44

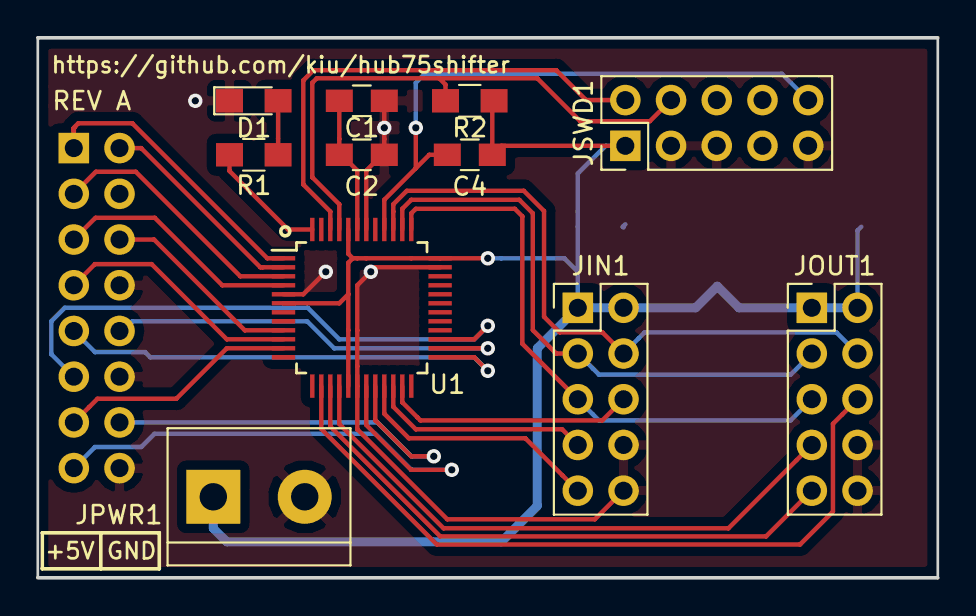
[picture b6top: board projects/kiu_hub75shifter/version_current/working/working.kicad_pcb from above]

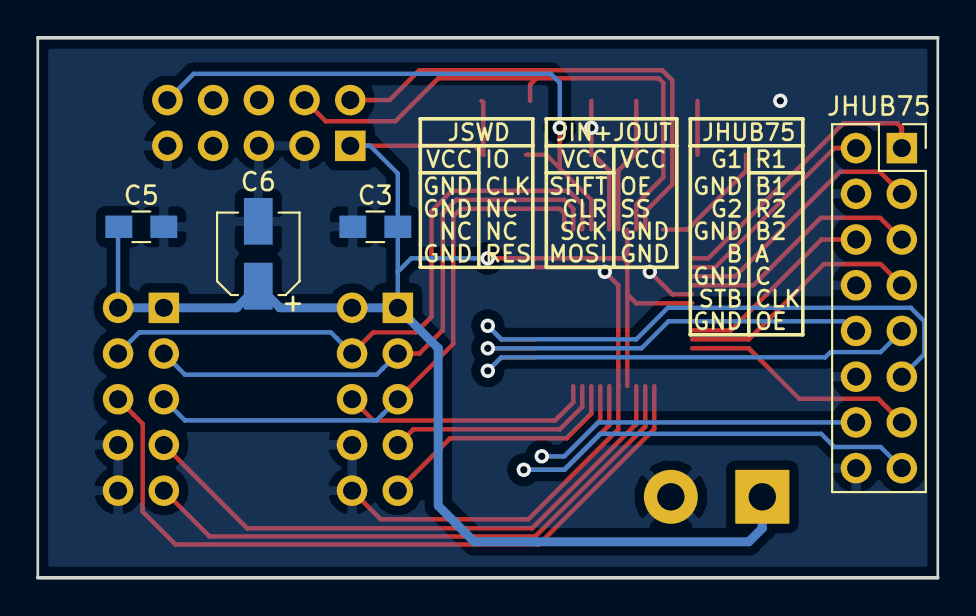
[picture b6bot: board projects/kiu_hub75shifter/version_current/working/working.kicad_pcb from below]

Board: 2 copper layers, 50.0 x 30.0 mm, 15 parts (4 on the bottom side), 29 nets.

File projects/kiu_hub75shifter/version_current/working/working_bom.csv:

"Id";"Designator";"Footprint";"Quantity";"Designation";"Supplier and ref";
1;"C1,C3,C5";"C_0805_HandSoldering";3;"100nF";;;
2;"C2";"C_0805_HandSoldering";1;"1uF";;;
3;"JHUB75";"Socket_Strip_Straight_2x08_Pitch2.54mm";1;"Conn_02x08_Odd_Even";;;
4;"JIN1,JOUT1,JSWD1";"Pin_Header_Straight_2x05_Pitch2.54mm";3;"Conn_02x05_Odd_Even";;;
5;"U1";"TQFP-48_7x7mm_Pitch0.5mm";1;"SAMC20G17A-A";;;
6;"D1";"LED_0805_HandSoldering";1;"LED";;;
7;"R1";"R_0805_HandSoldering";1;"60R";;;
8;"C4";"C_0805_HandSoldering";1;"100pF";;;
9;"C6";"CP_Elec_4x5.7";1;"10uF";;;
10;"R2";"R_0805_HandSoldering";1;"1k";;;
11;"JPWR1";"TerminalBlock_bornier-2_P5.08mm";1;"Screw_Terminal_01x02";;;

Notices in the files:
projects/kazu_zamasu_usb4x3hub/version_current/working/working.kicad_sch:
CC-BY-SA
